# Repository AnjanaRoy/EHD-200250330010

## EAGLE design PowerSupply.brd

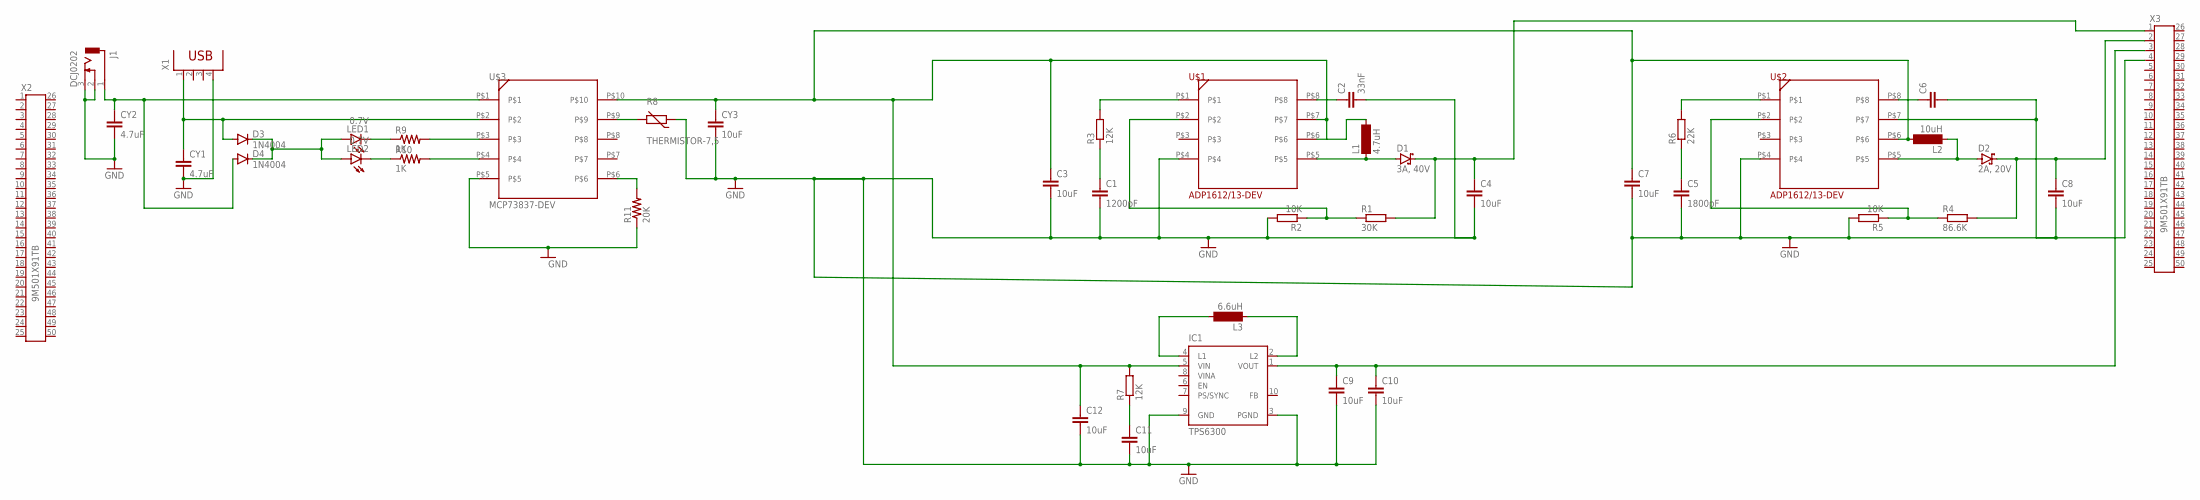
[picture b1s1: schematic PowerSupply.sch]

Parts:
C1: 1200pF; C2.5-2
C2: 33nF; C2.5-2
C3, C4, C7, C8: 10uF; C2.5-2
C5: 1800pF; C2.5-2
C6: C2.5/2; C2.5-2
C9, C10, C11, C12: 10uF; C2.5-3
CY1, CY2: 4.7uF; YC10B4
CY3: 10uF; YC10B4
D1: 3A, 40V; DO13M
D2: 2A, 20V; DO13M
D3, D4: 1N4004; DO41-10
IC1: TPS6300; DRC-S-PVSON-N10
J1: DCJ0202
L1: 4.7uH; SM-NE45
L2: 10uH; SM-NE45
L3: 6.6uH; SM-NE45
LED1, LED2: 0.7V; SMARTLED-TTW
R1: 30K; 0204V
R2, R5: 10K; 0204V
R3, R7: 12K; 0204V
R4: 86.6K; 0204V
R6: 22K; 0204V
R8: THERMISTOR-7,5; R-7,5
R9, R10: 1K; 0204V
R11: 20K; 0204V
U$1, U$2: ADP1612/13-DEV; ADP1612/13
U$3: MCP73837-DEV; MCP73837-FCI
X1: PN61729
X2, X3: 9M501X91TB; 9M501X91

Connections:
GND: C1.2, C2.2, C3.2, C4.2, C5.2, C6.2, C7.2, C8.2, C9.2, C10.2, C11.2, C12.2, CY1.2, CY2.2, CY3.2, IC1.3 (PGND), IC1.9 (GND), J1.2, J1.3, R2.2, R5.2, R8.1, R11.1, U$1.P$4, U$2.P$4, U$2.P$7, U$3.P$5, X1.4, X3.4
unnamed: C2.1, U$1.P$8
unnamed: R3.2, U$1.P$1
unnamed: C1.1, R3.1
unnamed: D1.A, L1.1, U$1.P$5
unnamed: C4.1, D1.C, R1.2, X3.1
unnamed: R1.1, R2.1, U$1.P$2
unnamed: R6.2, U$2.P$1
unnamed: C5.1, R6.1
unnamed: C8.1, D2.C, R4.2, X3.2
unnamed: C6.1, U$2.P$8
unnamed: D2.A, L2.1, U$2.P$5
unnamed: R4.1, R5.1, U$2.P$2
unnamed: C11.1, R7.1
unnamed: C3.1, C7.1, C12.1, CY3.1, IC1.5 (VIN), L1.2, L2.2, R7.2, U$1.P$6, U$1.P$7, U$2.P$6, U$3.P$10
unnamed: IC1.4 (L1), L3.2
unnamed: IC1.2 (L2), L3.1
unnamed: C9.1, C10.1, IC1.1 (VOUT), X3.3
unnamed: LED1.C@1 (C), R9.1
unnamed: LED2.C@1 (C), R10.1
unnamed: R10.2, U$3.P$4
unnamed: R9.2, U$3.P$3
unnamed: R11.2, U$3.P$6
unnamed: R8.2, U$3.P$9
unnamed: CY1.1, D3.A, U$3.P$2, X1.1
unnamed: D3.C, D4.C, LED1.A@1 (A), LED2.A@1 (A)
unnamed: CY2.1, D4.A, J1.1, U$3.P$1

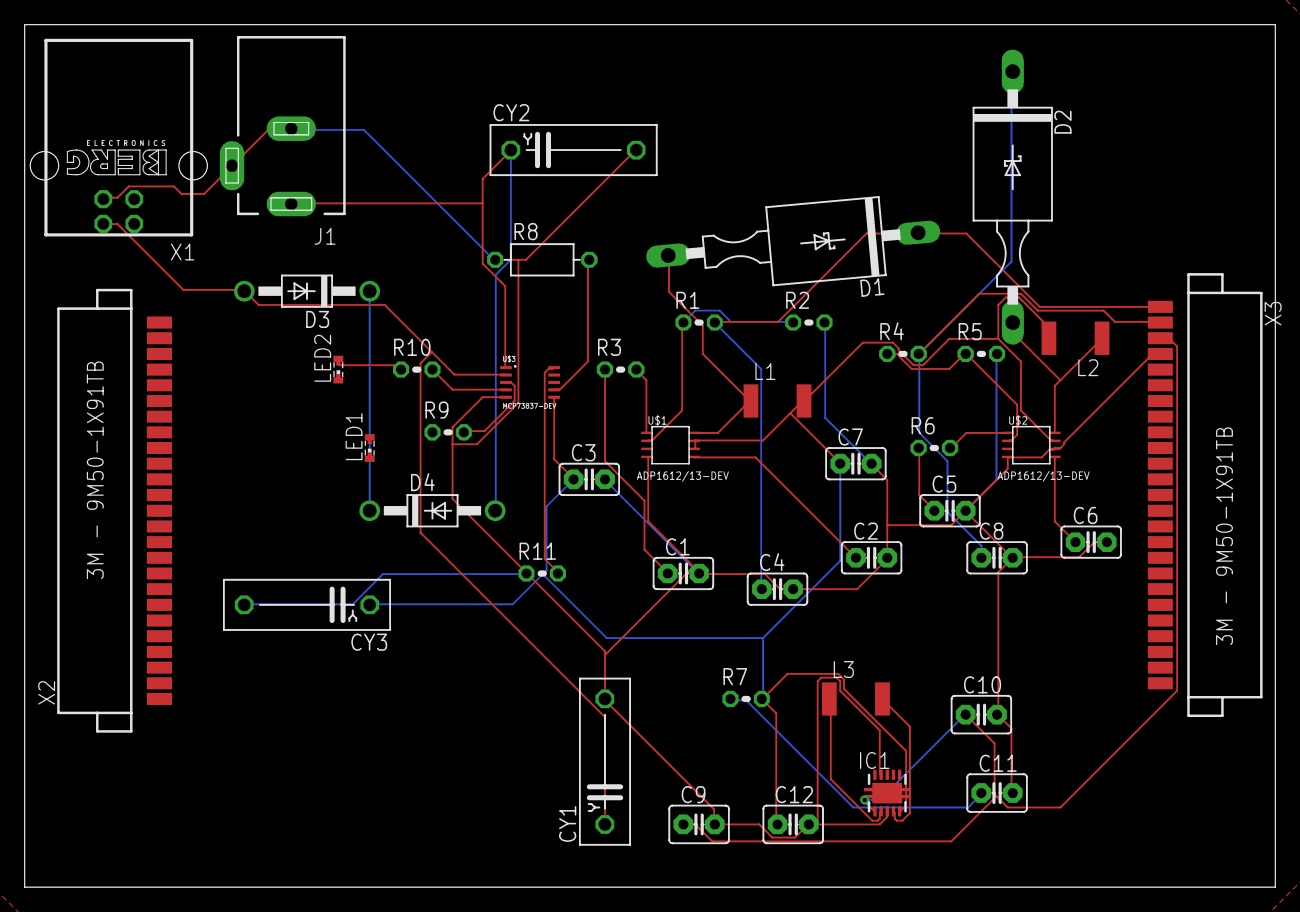
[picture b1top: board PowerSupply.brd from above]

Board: 2 copper layers, 101.3 x 69.8 mm, 43 parts (0 on the bottom side), 27 nets.

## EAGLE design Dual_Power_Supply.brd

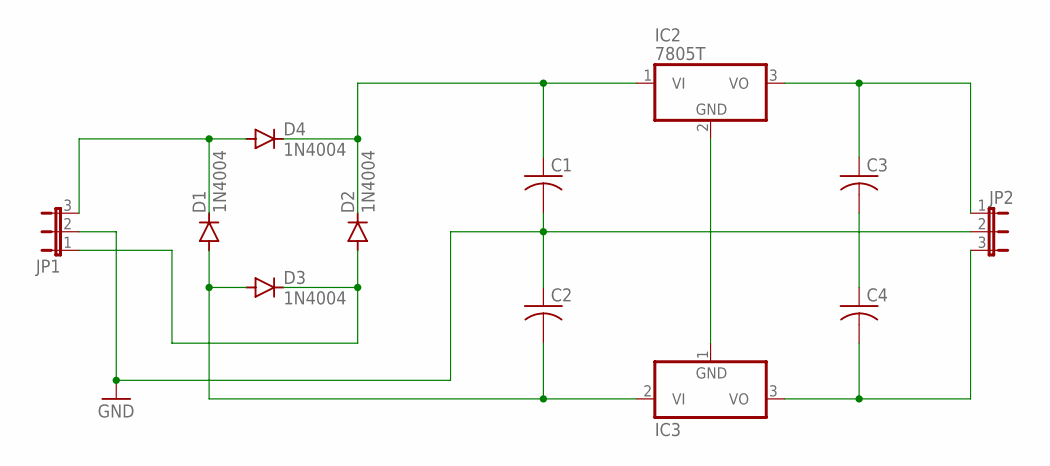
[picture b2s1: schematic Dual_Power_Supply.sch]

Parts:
C1, C2, C3, C4: C-US025-025X050; C025-025X050
D1, D2, D3, D4: 1N4004; DO41-10
IC2: 7805T; TO220H
IC3: 7905T; TO220H
JP1, JP2: JP2E; JP2

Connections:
GND: C1.2, C2.1, JP1.2, JP2.2
unnamed: D1.C, D4.A, JP1.3
unnamed: C2.2, D1.A, D3.A, IC3.2 (VI)
unnamed: C1.1, D2.C, D4.C, IC2.1 (VI)
unnamed: D2.A, D3.C, JP1.1
unnamed: C3.1, IC2.3 (VO), JP2.1
unnamed: IC2.2 (GND), IC3.1 (GND)
unnamed: C3.2, C4.1
unnamed: C4.2, IC3.3 (VO), JP2.3

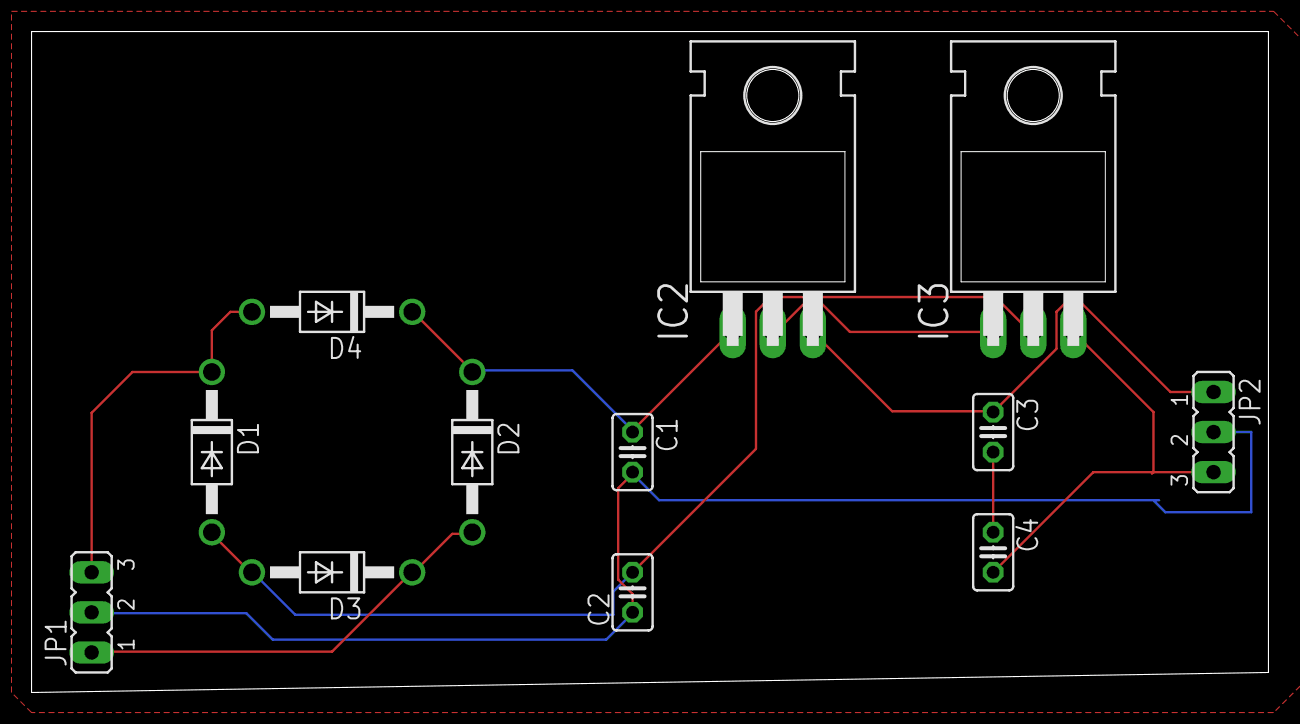
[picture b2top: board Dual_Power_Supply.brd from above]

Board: 2 copper layers, 78.4 x 41.9 mm, 12 parts (0 on the bottom side), 9 nets.

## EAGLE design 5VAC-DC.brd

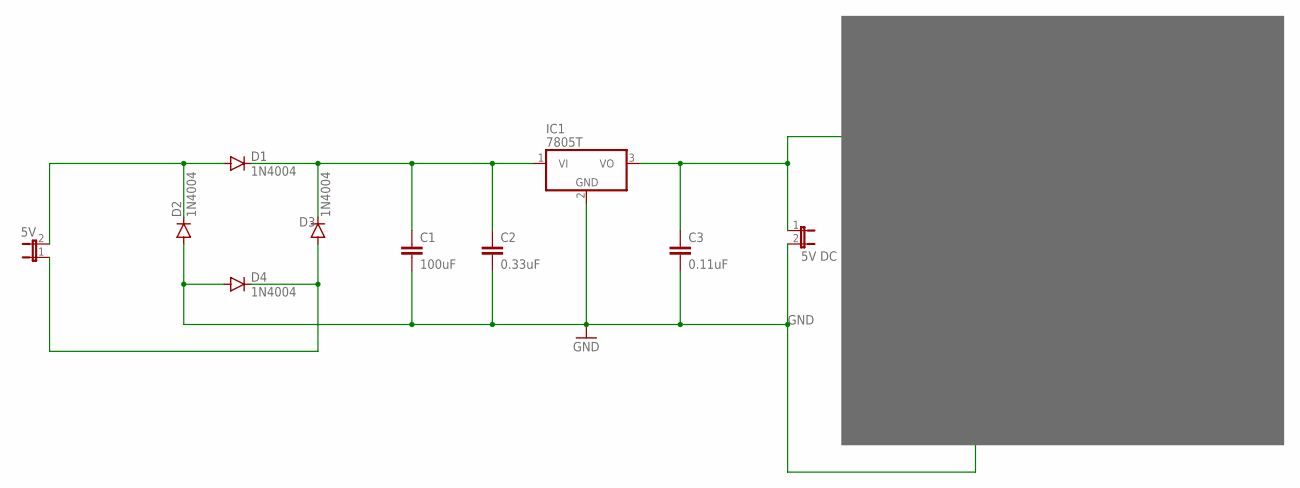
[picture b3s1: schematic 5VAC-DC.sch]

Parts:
C1: 100uF; C2.5-3
C2: 0.33uF; C2.5-3
C3: 0.11uF; C2.5-3
D1, D2, D3, D4: 1N4004; DO41-10
I/P: 5V; JP1
IC1: 7805T; TO220H
JP2: 5V DC; JP1
U$1: MEGA8L-DEV; TQFP-MEGA8

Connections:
GND: C1.2, C2.2, C3.2, D2.A, D4.A, IC1.2 (GND), JP2.2, U$1.P$9
unnamed: D1.A, D2.C, I/P.2
unnamed: D3.A, D4.C, I/P.1
unnamed: C1.1, C2.1, D1.C, D3.C, IC1.1 (VI)
unnamed: C3.1, IC1.3 (VO), JP2.1, U$1.P$1

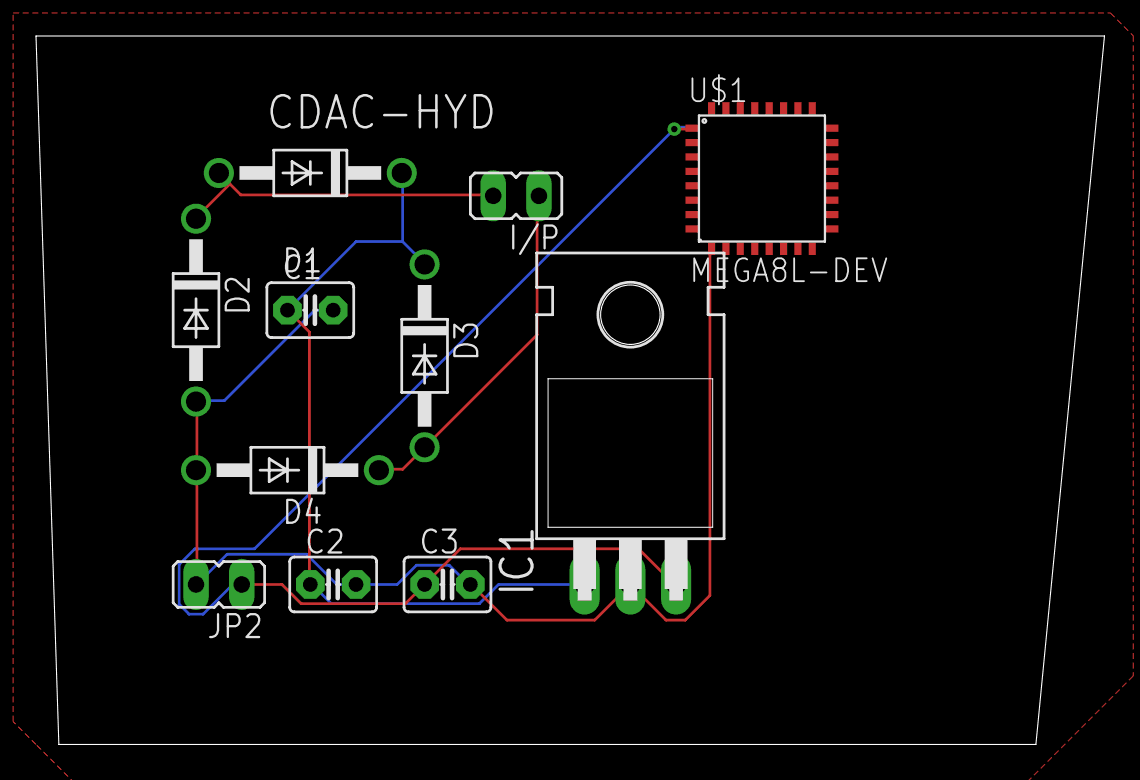
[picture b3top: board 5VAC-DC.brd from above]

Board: 2 copper layers, 59.4 x 39.4 mm, 11 parts (0 on the bottom side), 5 nets.
